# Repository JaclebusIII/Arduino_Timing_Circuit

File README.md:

# Arduino Timing Circuit
The purpose of this project is to trigger four different 3D cameras at 20 FPS with each camera offset by 2ms. The implementation that was used can be adapted to trigger up to 8 cameras at any frequency or time offset with just a few changes to the code. The code has been commented to make this as intuitive as possible. 

## Hardware Implementation
For the hardware, I used an Arduino Nano soldered onto a custom made PCB for quick and reliable wire connections. To complexity and cost down, the PCB design is meant to be milled from a small piece of single sided copper clad board on a desktop CNC mill. For the connectors, I used 8 barrel jacks, 4 of which are connected to analog pins and the other 4 connected to digital pins. This was done so that I could keep the board as small as possible with the widest wires possible to ensure proper connection. I mounted the Nano to the bottom of the board to make soldering the Nano as easy as possible and maximize the room for wires on the top.

Board files and images are included below. 

## Code Implementation 
To trigger the cameras, I used the Nano's hardware triggers along with a simple state machine to trigger the exposure of each individual camera. This means that the main "loop" function is completely empty and the function that actually does all the triggering is the Interrupt Service Routine or IRS. This is where the state machine is implemented. 

The timing parameters are set at the top of the code, and can be changed very easily for other timing needs. The two parameters are the compare match register or cmr and the numstates variable. The internal clock of the Arduino runs at 16GHZ and the cmr is used to subsample this internal clock at the rate of the camera offset frequency. The equation for ocr given frequency is given below:

    compare match register = [(Arduino clock speed 16,000,000Hz) / (interrupt frequency (Hz) * prescaler)] - 1

For my purposes, I used a prescaler of 1024 because the value of the cmr cannot exceed 256 due to hardware limitations and this allowed me to get enough timer precision. The prescaler is configured in the setup function at the bottom of the code. 

The numstates variable determines the camera's FPS. It is basically the number of subsampled clock ticks to wait between individual camera triggers. The equation of that variable is shown below.

    numstates = interrupt frequency (Hz) / Camera frequency 

The PCB board is not necessary to use the code and is simply there for quick and reliable connection to the Arduino

## Images

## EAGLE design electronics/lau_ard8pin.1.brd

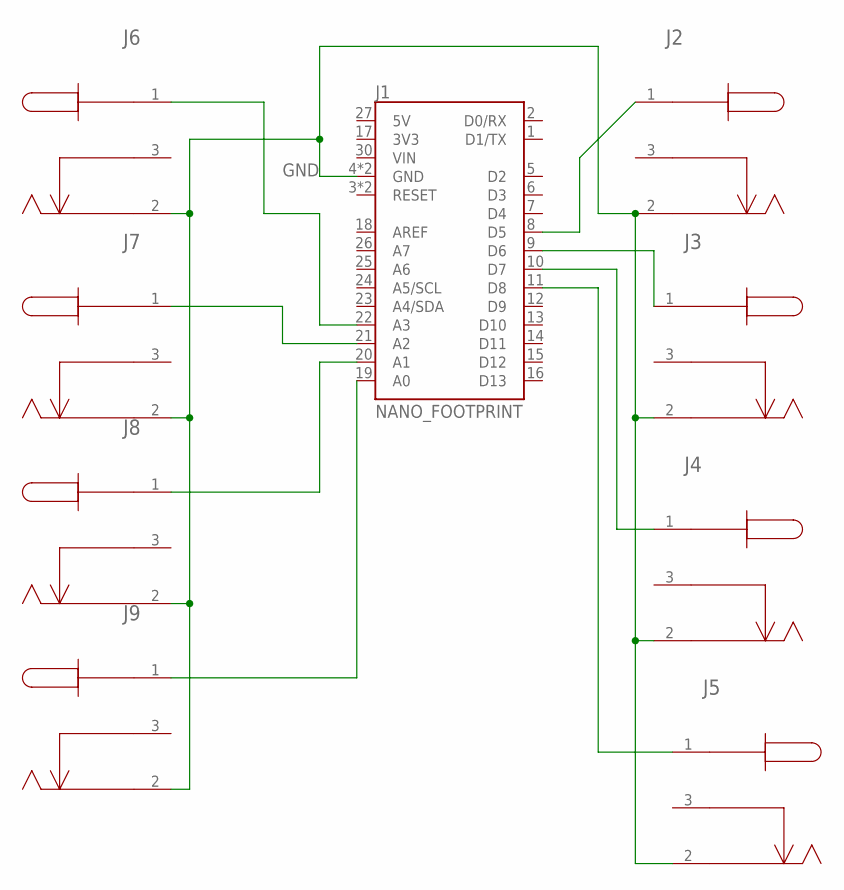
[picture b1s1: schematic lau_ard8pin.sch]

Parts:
J1: NANO_FOOTPRINT; NANO
J2, J3, J4, J5, J6, J7, J8, J9: 694106105102; CONN3_06105102_WRE

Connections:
GND: J1.4 (GND), J1.29 (GND), J2.2, J3.2, J4.2, J5.2, J6.2, J7.2, J8.2, J9.2
unnamed: J1.8 (D5), J2.1
unnamed: J1.9 (D6), J3.1
unnamed: J1.10 (D7), J4.1
unnamed: J1.11 (D8), J5.1
unnamed: J1.19 (A0), J9.1
unnamed: J1.20 (A1), J8.1
unnamed: J1.21 (A2), J7.1
unnamed: J1.22 (A3), J6.1

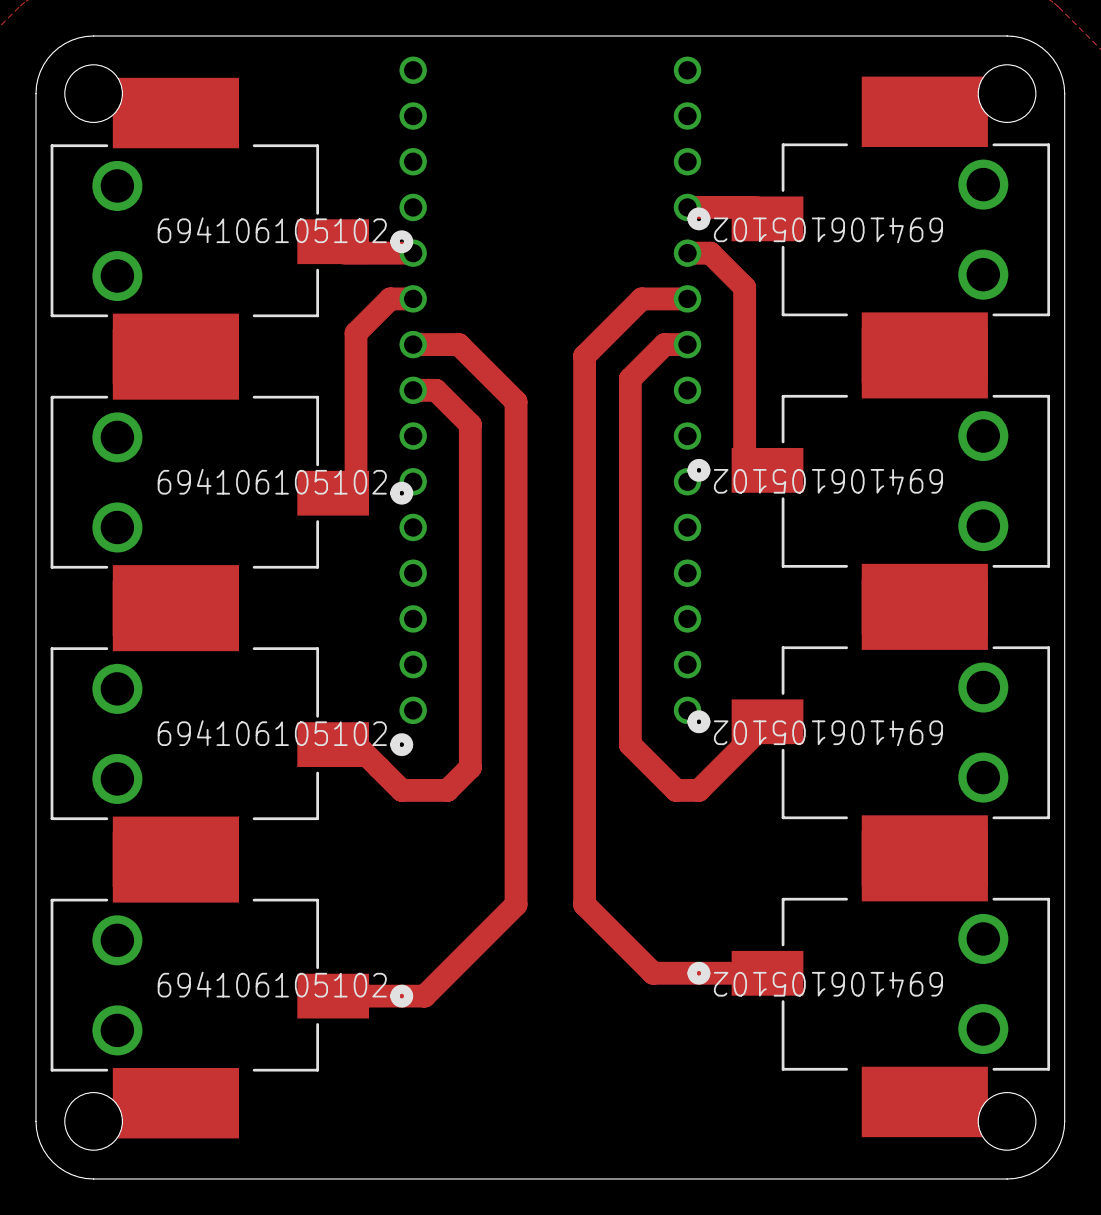
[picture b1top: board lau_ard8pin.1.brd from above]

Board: 2 copper layers, 57.1 x 63.5 mm, 9 parts (1 on the bottom side), 9 nets.

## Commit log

2023-01-31 Quick fixes for DLau
2023-01-31 Added proper readme. Project basically done
2023-03-06 Fixed pin outs for digital

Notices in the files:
parts and their libraries:
SparkFun-Boards: Licensing: Creative Commons ShareAlike 4.0 International - https://creativecommons.org/licenses/by-sa/4.0
COPYRIGHT: Copyright (C) 2022 Ultra Librarian. All rights reserved.
